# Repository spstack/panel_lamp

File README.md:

# Instrument Panel Lamp

I got this old instrument panel out of a printing press that was (unfortunately) being scrapped.
Decided to make it into a cool looking lamp so it's not only a neat display, but also somewhat functional.

I'm honestly not sure what the panel controlled on the old printing press, but it's pretty cool looking and
has some super satisfying switches to press.

It uses all of the original knobs and buttons to control various aspects of the lamp.

The toggle switch in the center is the main on/off switch for the whole thing. It's wired through one
of the fuses on the front panel as well.

The left knob controls the brightness of the main lamp bulb. It's an autotransformer, so it can just
be directly hooked up to the bulb to control brightness.

The other switches/knobs are tied to an arduino that controls back-lighting LEDs

## Schematic

## PCB Layout

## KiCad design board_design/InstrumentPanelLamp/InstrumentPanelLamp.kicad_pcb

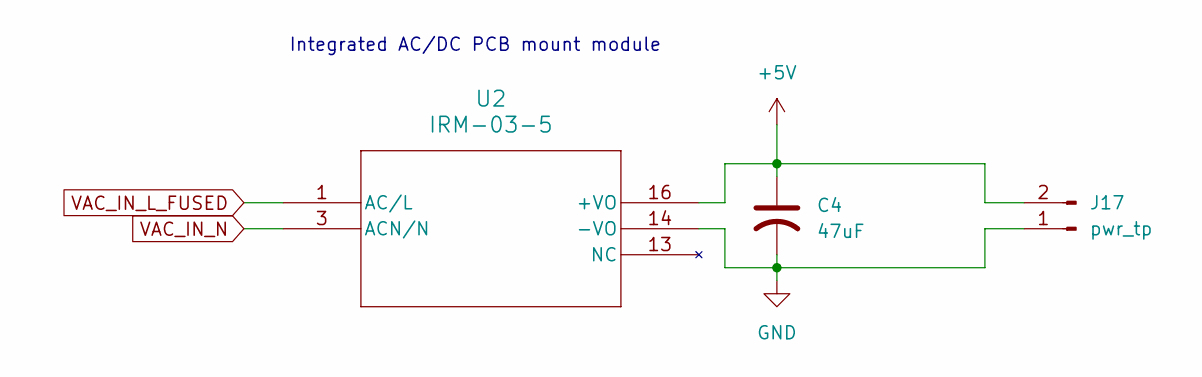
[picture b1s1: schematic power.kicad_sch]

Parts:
C4: 47uF; CP_Radial_D8.0mm_P3.50mm
J17: pwr_tp; PinHeader_1x02_P2.54mm_Vertical
U2: IRM-03-5; IRM-03_MWU

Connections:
+5V: C4.1, J17.2, U2.16 (+VO); also elsewhere on the board
GND: C4.2, J17.1, U2.14 (-VO); also elsewhere on the board
VAC_IN_L_FUSED: U2.1 (AC/L); also elsewhere on the board
VAC_IN_N: U2.3 (ACN/N); also elsewhere on the board

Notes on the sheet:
Integrated AC/DC PCB mount module

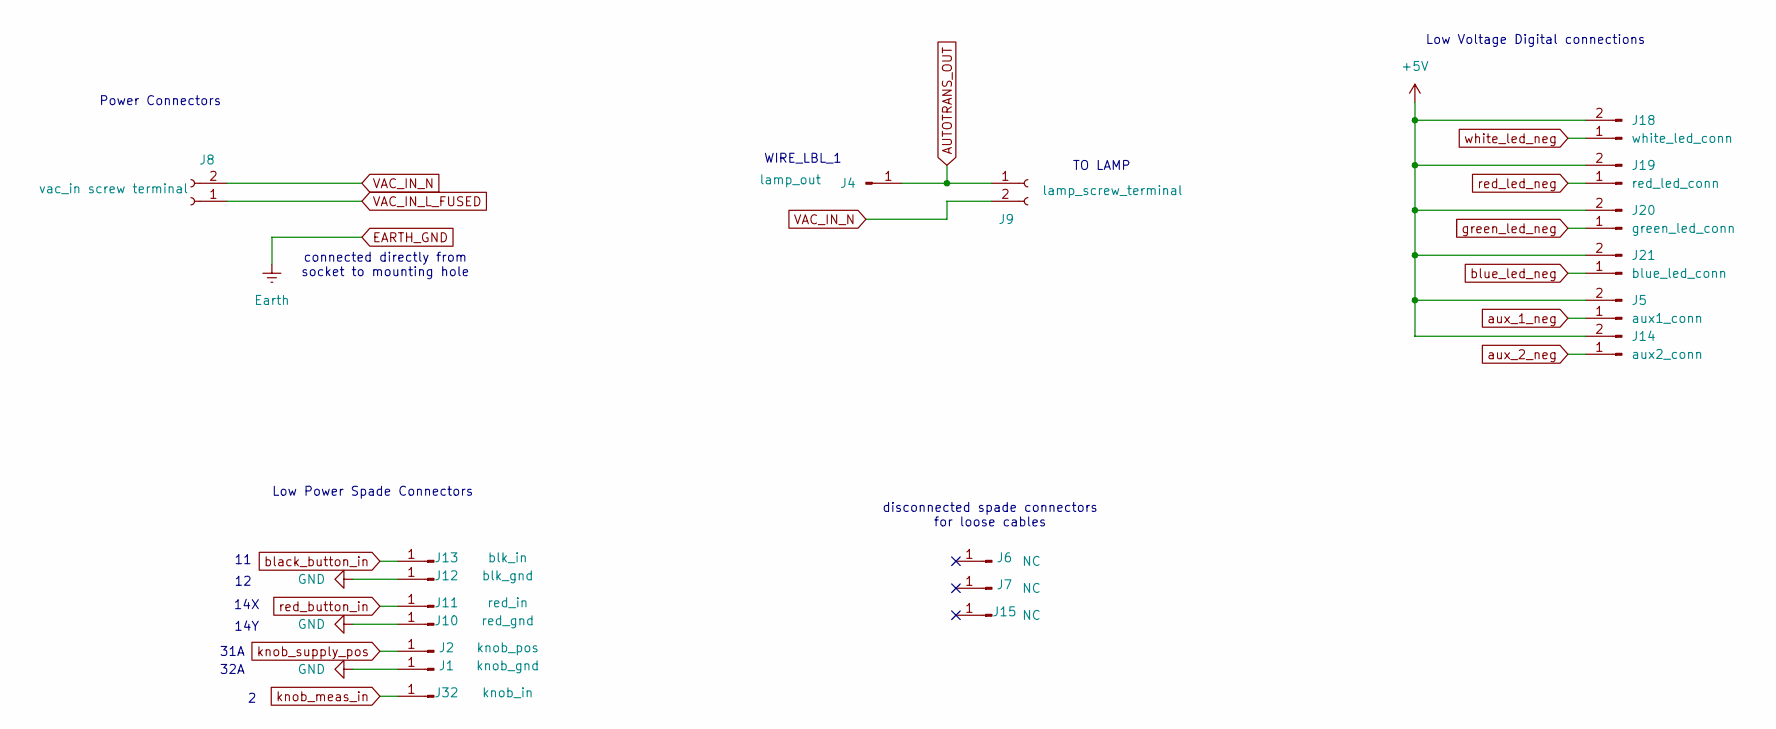
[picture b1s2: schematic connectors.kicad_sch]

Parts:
J1: knob_gnd; Keystone_4914_90deg_spade_male
J2: knob_pos; Keystone_4914_90deg_spade_male
J4: lamp_out; Keystone_4914_90deg_spade_male
J5: aux1_conn; PinHeader_1x02_P2.54mm_Vertical
J6, J7, J15: NC; Keystone_4914_90deg_spade_male
J8: vac_in screw terminal; CONN2_1102030_OST
J9: lamp_screw_terminal; CONN2_1102030_OST
J10: red_gnd; Keystone_4914_90deg_spade_male
J11: red_in; Keystone_4914_90deg_spade_male
J12: blk_gnd; Keystone_4914_90deg_spade_male
J13: blk_in; Keystone_4914_90deg_spade_male
J14: aux2_conn; PinHeader_1x02_P2.54mm_Vertical
J18: white_led_conn; PinHeader_1x02_P2.54mm_Vertical
J19: red_led_conn; PinHeader_1x02_P2.54mm_Vertical
J20: green_led_conn; PinHeader_1x02_P2.54mm_Vertical
J21: blue_led_conn; PinHeader_1x02_P2.54mm_Vertical
J32: knob_in; Keystone_4914_90deg_spade_male

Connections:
+5V: J5.2, J14.2, J18.2, J19.2, J20.2, J21.2; also elsewhere on the board
AUTOTRANS_OUT: J4.1, J9.1
GND: J1.1, J10.1, J12.1; also elsewhere on the board
VAC_IN_L_FUSED: J8.1; also elsewhere on the board
VAC_IN_N: J8.2, J9.2; also elsewhere on the board
aux_1_neg: J5.1; also elsewhere on the board
aux_2_neg: J14.1; also elsewhere on the board
black_button_in: J13.1; also elsewhere on the board
blue_led_neg: J21.1; also elsewhere on the board
green_led_neg: J20.1; also elsewhere on the board
knob_meas_in: J32.1; also elsewhere on the board
knob_supply_pos: J2.1; also elsewhere on the board
red_button_in: J11.1; also elsewhere on the board
red_led_neg: J19.1; also elsewhere on the board
white_led_neg: J18.1; also elsewhere on the board

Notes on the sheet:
31A
14X
Power Connectors
14Y
Low Voltage Digital connections
32A
WIRE_LBL_1
Low Power Spade Connectors
connected directly from socket to mounting hole
disconnected spade connectors for loose cables
TO LAMP

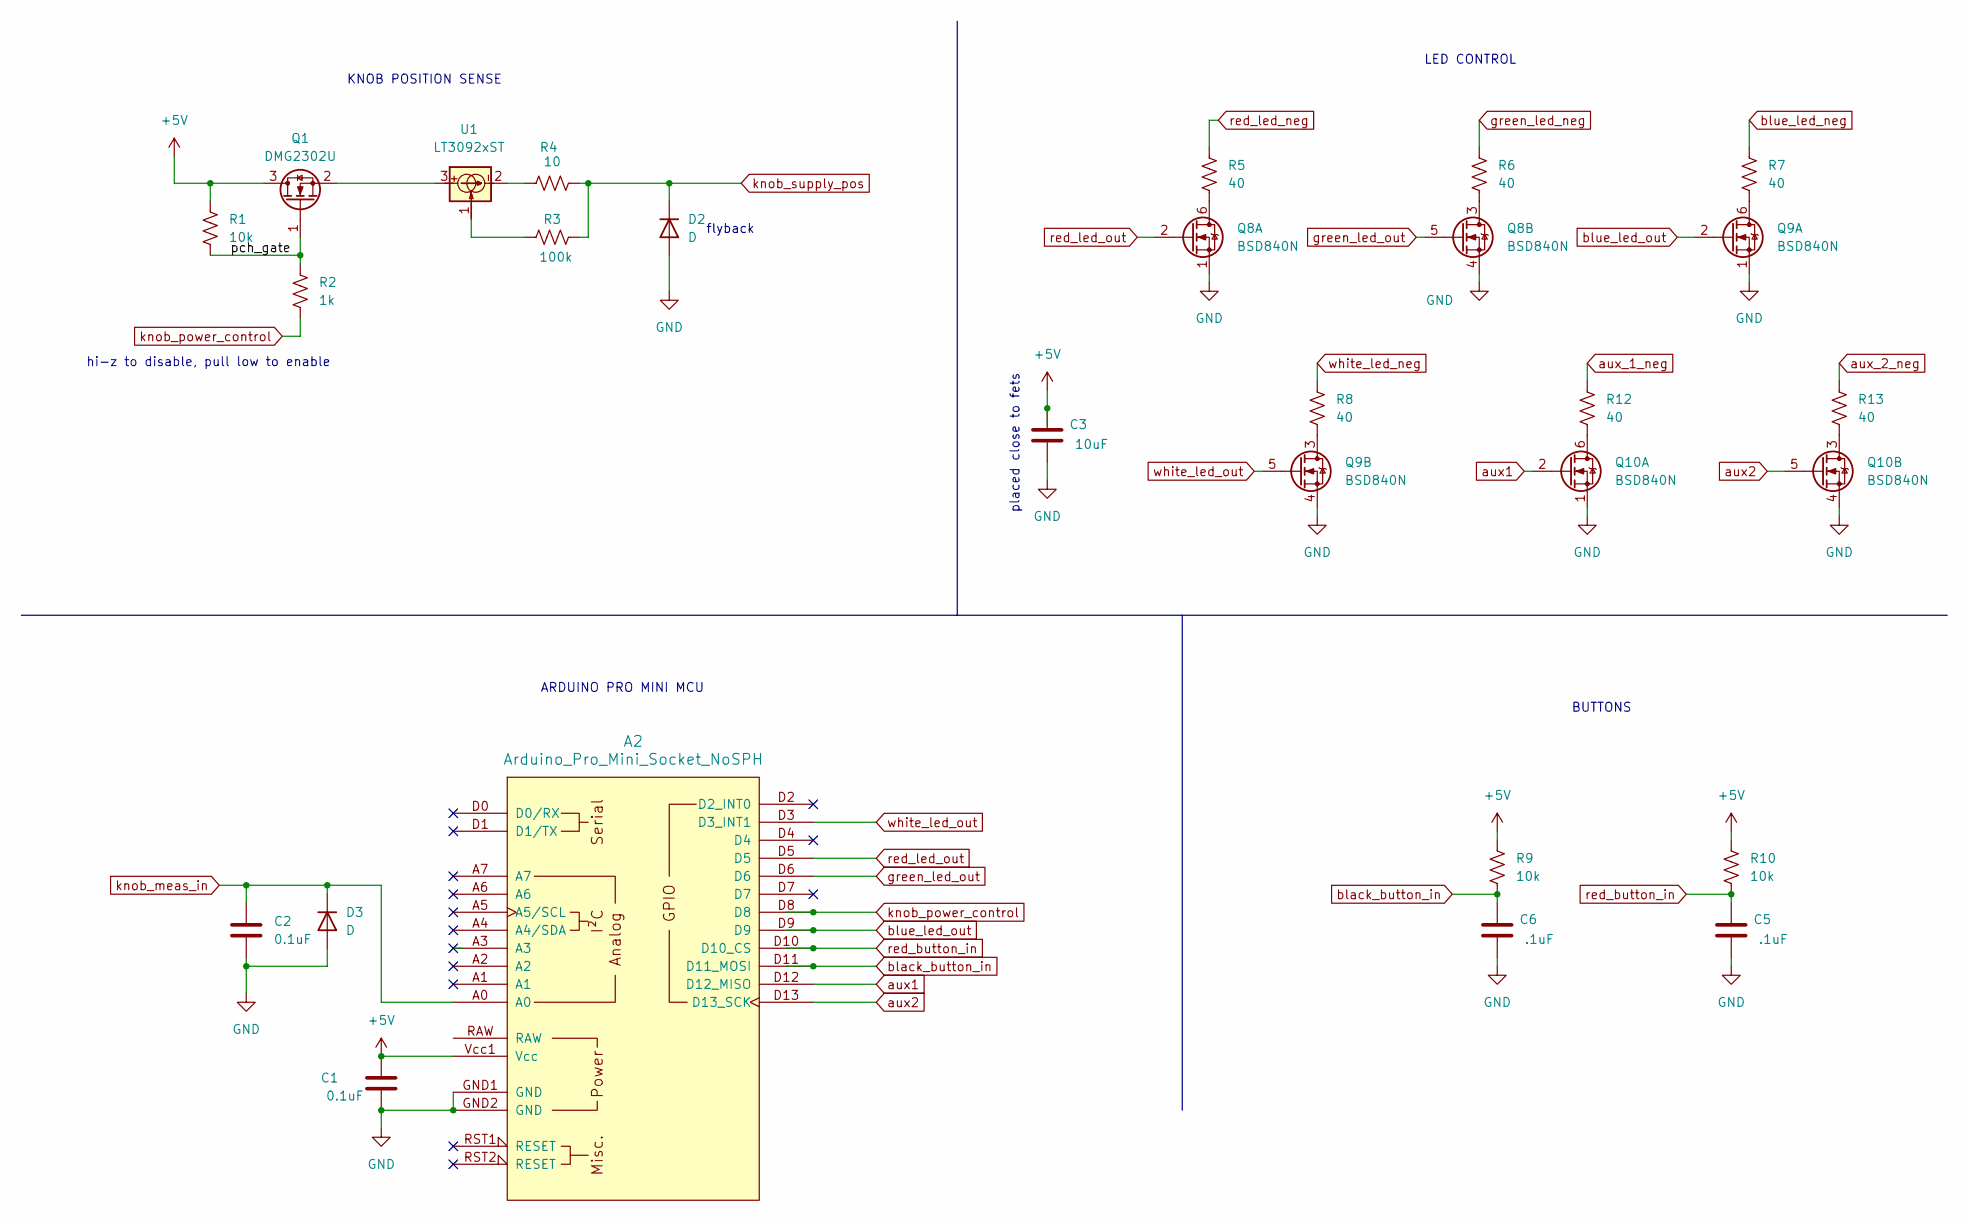
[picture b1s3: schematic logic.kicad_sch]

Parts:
A2: Arduino_Pro_Mini_Socket_NoSPH
C1, C2: 0.1uF; C_0805_2012Metric_Pad1.18x1.45mm_HandSolder
C3: 10uF; C_0805_2012Metric_Pad1.18x1.45mm_HandSolder
C5, C6: .1uF; C_0805_2012Metric_Pad1.18x1.45mm_HandSolder
D2, D3: D; D_SMA_Handsoldering
Q1: DMG2302U; SOT-23
Q8, Q9, Q10: BSD840N; SOT-363_SC-70-6
R1, R9, R10: 10k; R_0805_2012Metric_Pad1.20x1.40mm_HandSolder
R2: 1k; R_0805_2012Metric_Pad1.20x1.40mm_HandSolder
R3: 100k; R_0805_2012Metric_Pad1.20x1.40mm_HandSolder
R4: 10; R_0805_2012Metric_Pad1.20x1.40mm_HandSolder
R5, R6, R7, R8, R12, R13: 40; R_0805_2012Metric_Pad1.20x1.40mm_HandSolder
U1: LT3092xST; SOT-223-3_TabPin2

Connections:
+5V: A2.Vcc1 (Vcc), C1.1, C3.2, Q1.3 (D), R1.1, R9.1, R10.1; also elsewhere on the board
/logic/pch_gate: Q1.1 (G), R1.2, R2.1
GND: A2.GND1 (GND), A2.GND2 (GND), C1.2, C2.1, C3.1, C5.1, C6.1, D2.2 (A), D3.2 (A), Q8.1 (S), Q8.4 (S), Q9.1 (S), Q9.4 (S), Q10.1 (S), Q10.4 (S); also elsewhere on the board
unnamed: Q1.2 (S), U1.3
unnamed: Q8.6 (D), R5.2
unnamed: Q8.3 (D), R6.2
unnamed: Q9.6 (D), R7.2
unnamed: Q9.3 (D), R8.2
unnamed: Q10.6 (D), R12.2
unnamed: Q10.3 (D), R13.2
unnamed: R3.2, U1.1
unnamed: R4.2, U1.2
aux1: A2.D12 (D12_MISO), Q10.2 (G)
aux2: A2.D13 (D13_SCK), Q10.5 (G)
aux_1_neg: R12.1; also elsewhere on the board
aux_2_neg: R13.1; also elsewhere on the board
black_button_in: A2.D11 (D11_MOSI), C6.2, R9.2; also elsewhere on the board
blue_led_neg: R7.1; also elsewhere on the board
blue_led_out: A2.D9, Q9.2 (G)
green_led_neg: R6.1; also elsewhere on the board
green_led_out: A2.D6, Q8.5 (G)
knob_meas_in: A2.A0, C2.2, D3.1 (K); also elsewhere on the board
knob_power_control: A2.D8, R2.2
knob_supply_pos: D2.1 (K), R3.1, R4.1; also elsewhere on the board
red_button_in: A2.D10 (D10_CS), C5.2, R10.2; also elsewhere on the board
red_led_neg: R5.1; also elsewhere on the board
red_led_out: A2.D5, Q8.2 (G)
white_led_neg: R8.1; also elsewhere on the board
white_led_out: A2.D3 (D3_INT1), Q9.5 (G)

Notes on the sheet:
flyback
KNOB POSITION SENSE
placed close to fets
BUTTONS
ARDUINO PRO MINI MCU
LED CONTROL
hi-z to disable, pull low to enable

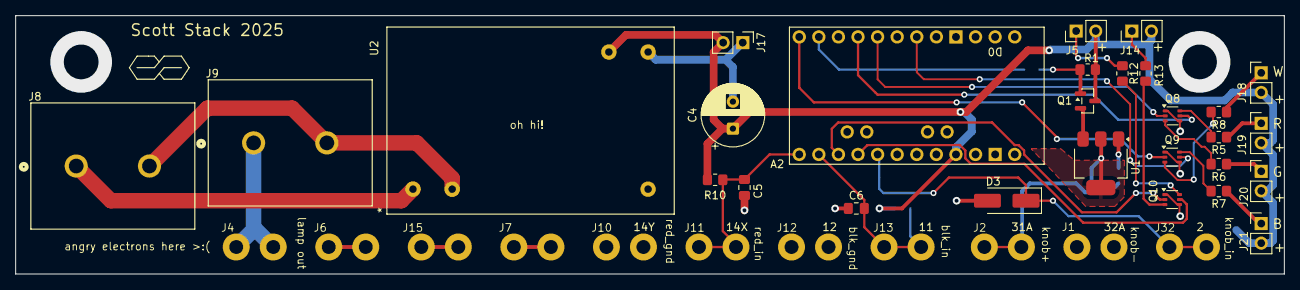
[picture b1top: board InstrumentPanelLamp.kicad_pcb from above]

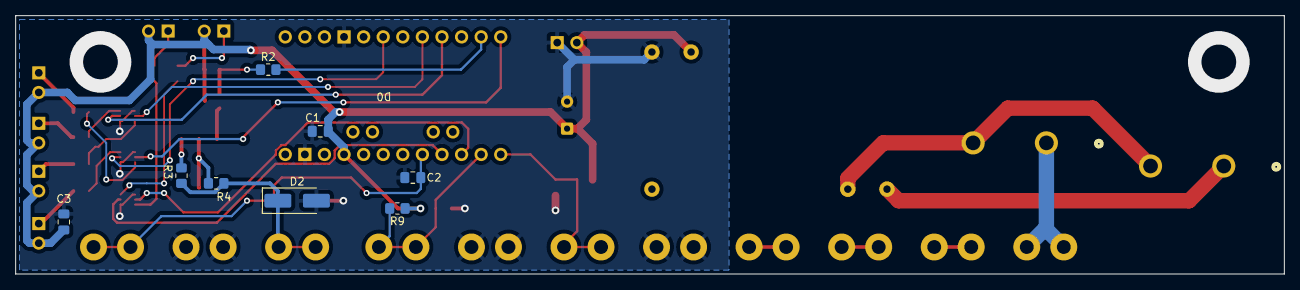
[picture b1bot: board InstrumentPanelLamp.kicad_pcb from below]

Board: 2 copper layers, 164.5 x 33.5 mm, 47 parts (8 on the bottom side), 32 nets.

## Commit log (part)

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2025-10-26 Fix a bunch of bugs, and get RGB cycling working properly
2025-11-15 Move pcb files to new board_design directory, add arduino sketch, and update pico LampPicoProject
    Lots of updates here because I forgot to commit for a while.
    - Updating Pico version of the code to actually be functional (now has LED updates and knob reading)
    - Adding Arduino sketch for controlling the lamp via Arduino because I might need to switch
    to a Pro mini for space reasons on the pcb
    - Move PCB design to new board_design directory structure
    - Finish the schematic for thew PCB design that uses the PI Pico
2025-11-18 Complete initial version of Arduino code and initial PCB placement
    The arduino sketch is now as functional as the old version was.
    The kicab pcb file has the initial placement of components done as
    well using the updated Arduino pro mini as the MCU.
2026-01-28 ardiuino sketch: implement smooth RGB color cycling for the panel lamp and fix brightness
    - Adding RGB color cycling with smooth transitions between colors
    - Add states for Red, Green, and Blue static colors
    - Fix brightness calculation to use full 0-255 range for PWM control
2026-01-28 board: Update board/sch design files with 3d model changes
2026-05-09 Cleanup git repository in preparation for adding to github
    - remove the Pico project that is no longer used
    - add larger files to git lfs
    - update .gitignore to ignore more files that are not needed in the repository
    - add gerber files and step files for the PCB release to the repository
    - generate a PDF of the schematic and add it to the repository
